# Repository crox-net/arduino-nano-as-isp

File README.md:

# Arduino Nano as ISP

A simple PCB to use an Arduino Nano as ISP, together with a "pogo pins" adapter.

The board has the "standard" ICSP header, as well as a 01x06/2.54mm header with the same pinout as the SparkFun adapter (see below). The latest revision of the board also includes its own pogo pins adapter, that can be used instead of the SparkFun one and that is secured to the main PBC with screws, making the setup more compact and stable. The first version had a header for a jumper which allowed you to connect the V+ pin either to 5V or 3.3V, this has now been replaced by a solder joint which connects V+ to 5V by default (you need to cut the small trace between the two corresponding pads of the JP2 solder joint if you don't want this). Beware that the data pins will be 5V in any case!

The other connections are as follows:
- D7 -> LED1
- D8 -> LED2
- D9 -> LED3
- D10 -> RESET
- D11 -> MOSI
- D12 -> MISO
- D13 -> SCK

The version 1.1 also adds C1, a 10uF capacitor between the RST and GND pins of the Arduino Nano (see below). It can be disabled by cutting the trace between the two pads of the JP1 solder joint.

As of Arduino 1.8.13, you can use the ArduinoISP sketch from the built-in examples unchanged. Unless C1 is disabled, you need to press "reset" on the Arduino Nano shortly before clicking "Upload" in the Arduino IDE for the sketch to upload successfully.

The SMD components are 0805 (2012 metric) with somehow bigger pads to allow for hand soldering. The LED are optional though, the board will work equally well without them. I use this [Arduino Nano clone](https://s.click.aliexpress.com/e/_Af7AwF) from RobotDyn, but any compatible board will do.

### First published version

Initially, I designed this because I wanted something easy (and relatively inexpensive) to use in combination with the [SparkFun ISP Pogo Adapter](https://www.sparkfun.com/products/11591).

I use it i.a. to program my [KeyChainino](https://www.keychainino.com/):

### Capacitor between RST and GND
In order to be able to flash the Arduino bootloader to the [Lora Button board](https://github.com/crox-net/lora-button-example), I had to add a 10uF capacitor between the RST and GND pins:

This is documented i.a. here: [ArduinoISP / how to wire your boards](https://www.arduino.cc/en/Tutorial/BuiltInExamples/ArduinoISP#how-to-wire-your-boards).

The current revision of the board includes the footprint for such a capacitor (C1).

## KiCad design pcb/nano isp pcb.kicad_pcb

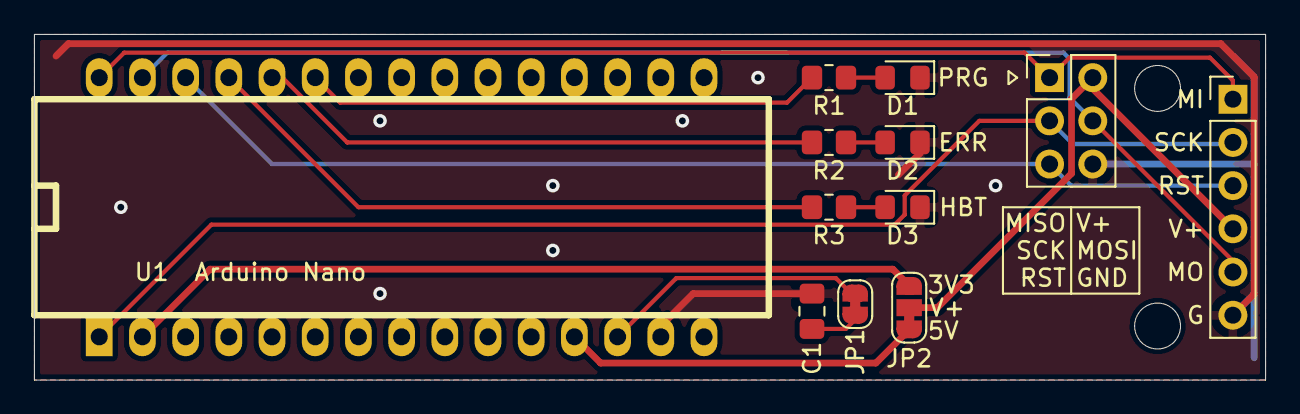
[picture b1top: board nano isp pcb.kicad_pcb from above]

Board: 2 copper layers, 72.4 x 20.3 mm, 14 parts (0 on the bottom side), 16 nets.

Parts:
C1: C; C_0805_2012Metric_Pad1.18x1.45mm_HandSolder
D1, D2, D3: LED; LED_0805_2012Metric_Pad1.15x1.40mm_HandSolder
J2: Conn_01x06; PinHeader_1x06_P2.54mm_Vertical
J3: Conn_02x03_Top_Bottom; PinHeader_2x03_P2.54mm_Vertical
JP1: SolderJumper_2_Bridged; SolderJumper-2_P1.3mm_Bridged_RoundedPad1.0x1.5mm
JP2: SolderJumper_3_Bridged12; SolderJumper-3_P1.3mm_Bridged12_RoundedPad1.0x1.5mm
R1, R2, R3: R; R_0805_2012Metric_Pad1.20x1.40mm_HandSolder
U1: arduino_nano; arduino_mini
h1, h2: MountingHole_2.7mm_M2.5

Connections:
+3V3: JP2.3, U1.2
+5V: JP2.1, U1.12
GND: C1.2, D1.1, D2.1, D3.1, J2.6, J3.6, U1.14, U1.19
unnamed: C1.1, JP1.1
unnamed: D1.2, R1.2
unnamed: D2.2, R2.2
unnamed: D3.2, R3.2
unnamed: J2.1, J3.1, U1.30
unnamed: J2.2, J3.2, U1.1
unnamed: J2.3, J3.3, U1.28
unnamed: J2.4, J3.4, JP2.2
unnamed: J2.5, J3.5, U1.29
unnamed: JP1.2, U1.13
unnamed: R1.1, U1.25
unnamed: R2.1, U1.26
unnamed: R3.1, U1.27

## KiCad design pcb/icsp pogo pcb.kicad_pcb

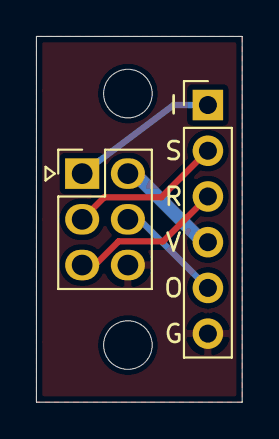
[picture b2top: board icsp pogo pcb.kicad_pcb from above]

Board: 2 copper layers, 11.4 x 20.3 mm, 4 parts (0 on the bottom side), 6 nets.

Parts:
J1: Conn_01x06; PinHeader_1x06_P2.54mm_Vertical
J2: Conn_02x03_Top_Bottom; PinHeader_2x03_P2.54mm_Vertical
h1, h2: MountingHole_2.7mm_M2.5

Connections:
GND: J1.6, J2.6
unnamed: J1.1, J2.1
unnamed: J1.2, J2.2
unnamed: J1.3, J2.3
unnamed: J1.5, J2.5
VCC: J1.4, J2.4

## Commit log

2021-02-14 added info about capacitor between RST and GND
2021-03-20 Added C1 capacitor, changed jumper to solder joint, added own pogo pins adapter.
2021-03-21 Fixing images links

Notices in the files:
pcb/icsp pogo pcb.kicad_pcb:
CC BY-SA
pcb/nano isp pcb.kicad_pcb:
CC BY-SA A. Suter
